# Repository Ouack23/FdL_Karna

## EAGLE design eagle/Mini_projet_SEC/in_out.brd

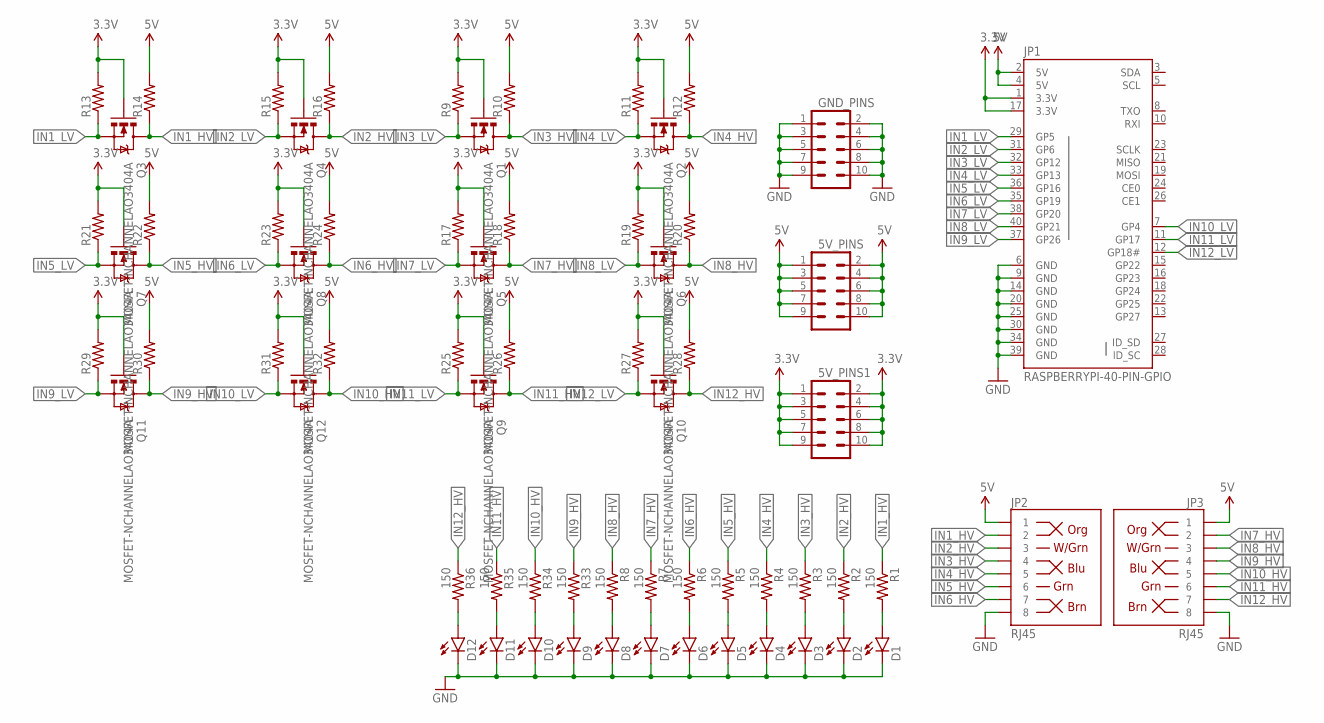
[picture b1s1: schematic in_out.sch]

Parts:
5V_PINS, 5V_PINS1: M05X2PTH; AVR_ICSP
D1, D2, D3, D4, D5, D6, D7, D8, D9, D10, D11, D12: LED5MM
GND_PINS: M05X2PTH; AVR_ICSP
JP1: RASPBERRYPI-40-PIN-GPIO; 2X20-SHROUDED
JP2, JP3: RJ45; RJ45-8
Q1, Q2, Q3, Q4, Q5, Q6, Q7, Q8, Q9, Q10, Q11, Q12: MOSFET-NCHANNELAO3404A; SOT23-3
R1, R2, R3, R4, R5, R6, R7, R8, R33, R34, R35, R36: 150; AXIAL-0.3EZ
R9, R10, R11, R12, R13, R14, R15, R16, R17, R18, R19, R20, R21, R22, R23, R24, R25, R26, R27, R28, R29, R30, R31, R32: RESISTORPTH-1/4W; AXIAL-0.4

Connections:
3.3V: 5V_PINS1.1, 5V_PINS1.2, 5V_PINS1.3, 5V_PINS1.4, 5V_PINS1.5, 5V_PINS1.6, 5V_PINS1.7, 5V_PINS1.8, 5V_PINS1.9, 5V_PINS1.10, JP1.1 (3.3V), JP1.17 (3.3V), Q1.1 (G), Q2.1 (G), Q3.1 (G), Q4.1 (G), Q5.1 (G), Q6.1 (G), Q7.1 (G), Q8.1 (G), Q9.1 (G), Q10.1 (G), Q11.1 (G), Q12.1 (G), R9.P$2 (2), R11.P$2 (2), R13.P$2 (2), R15.P$2 (2), R17.P$2 (2), R19.P$2 (2), R21.P$2 (2), R23.P$2 (2), R25.P$2 (2), R27.P$2 (2), R29.P$2 (2), R31.P$2 (2)
5V: 5V_PINS.1, 5V_PINS.2, 5V_PINS.3, 5V_PINS.4, 5V_PINS.5, 5V_PINS.6, 5V_PINS.7, 5V_PINS.8, 5V_PINS.9, 5V_PINS.10, JP1.2 (5V), JP1.4 (5V), JP2.1, JP3.1, R10.P$2 (2), R12.P$2 (2), R14.P$2 (2), R16.P$2 (2), R18.P$2 (2), R20.P$2 (2), R22.P$2 (2), R24.P$2 (2), R26.P$2 (2), R28.P$2 (2), R30.P$2 (2), R32.P$2 (2)
GND: D1.K (C), D2.K (C), D3.K (C), D4.K (C), D5.K (C), D6.K (C), D7.K (C), D8.K (C), D9.K (C), D10.K (C), D11.K (C), D12.K (C), GND_PINS.1, GND_PINS.2, GND_PINS.3, GND_PINS.4, GND_PINS.5, GND_PINS.6, GND_PINS.7, GND_PINS.8, GND_PINS.9, GND_PINS.10, JP1.6 (GND), JP1.9 (GND), JP1.14 (GND), JP1.20 (GND), JP1.25 (GND), JP1.30 (GND), JP1.34 (GND), JP1.39 (GND), JP2.8, JP3.8
IN1_HV: JP2.2, Q3.3 (D), R1.P$1 (1), R14.P$1 (1)
IN1_LV: JP1.29 (GP5), Q3.2 (S), R13.P$1 (1)
IN2_HV: JP2.3, Q4.3 (D), R2.P$1 (1), R16.P$1 (1)
IN2_LV: JP1.31 (GP6), Q4.2 (S), R15.P$1 (1)
IN3_HV: JP2.4, Q1.3 (D), R3.P$1 (1), R10.P$1 (1)
IN3_LV: JP1.32 (GP12), Q1.2 (S), R9.P$1 (1)
IN4_HV: JP2.5, Q2.3 (D), R4.P$1 (1), R12.P$1 (1)
IN4_LV: JP1.33 (GP13), Q2.2 (S), R11.P$1 (1)
IN5_HV: JP2.6, Q7.3 (D), R5.P$1 (1), R22.P$1 (1)
IN5_LV: JP1.36 (GP16), Q7.2 (S), R21.P$1 (1)
IN6_HV: JP2.7, Q8.3 (D), R6.P$1 (1), R24.P$1 (1)
IN6_LV: JP1.35 (GP19), Q8.2 (S), R23.P$1 (1)
IN7_HV: JP3.2, Q5.3 (D), R7.P$1 (1), R18.P$1 (1)
IN7_LV: JP1.38 (GP20), Q5.2 (S), R17.P$1 (1)
IN8_HV: JP3.3, Q6.3 (D), R8.P$1 (1), R20.P$1 (1)
IN8_LV: JP1.40 (GP21), Q6.2 (S), R19.P$1 (1)
IN9_HV: JP3.4, Q11.3 (D), R30.P$1 (1), R33.P$1 (1)
IN9_LV: JP1.37 (GP26), Q11.2 (S), R29.P$1 (1)
IN10_HV: JP3.5, Q12.3 (D), R32.P$1 (1), R34.P$1 (1)
IN10_LV: JP1.7 (GP4), Q12.2 (S), R31.P$1 (1)
IN11_HV: JP3.6, Q9.3 (D), R26.P$1 (1), R35.P$1 (1)
IN11_LV: JP1.11 (GP17), Q9.2 (S), R25.P$1 (1)
IN12_HV: JP3.7, Q10.3 (D), R28.P$1 (1), R36.P$1 (1)
IN12_LV: JP1.12 (GP18#), Q10.2 (S), R27.P$1 (1)
unnamed: D9.A, R33.P$2 (2)
unnamed: D10.A, R34.P$2 (2)
unnamed: D1.A, R1.P$2 (2)
unnamed: D2.A, R2.P$2 (2)
unnamed: D3.A, R3.P$2 (2)
unnamed: D4.A, R4.P$2 (2)
unnamed: D5.A, R5.P$2 (2)
unnamed: D6.A, R6.P$2 (2)
unnamed: D7.A, R7.P$2 (2)
unnamed: D8.A, R8.P$2 (2)
unnamed: D11.A, R35.P$2 (2)
unnamed: D12.A, R36.P$2 (2)

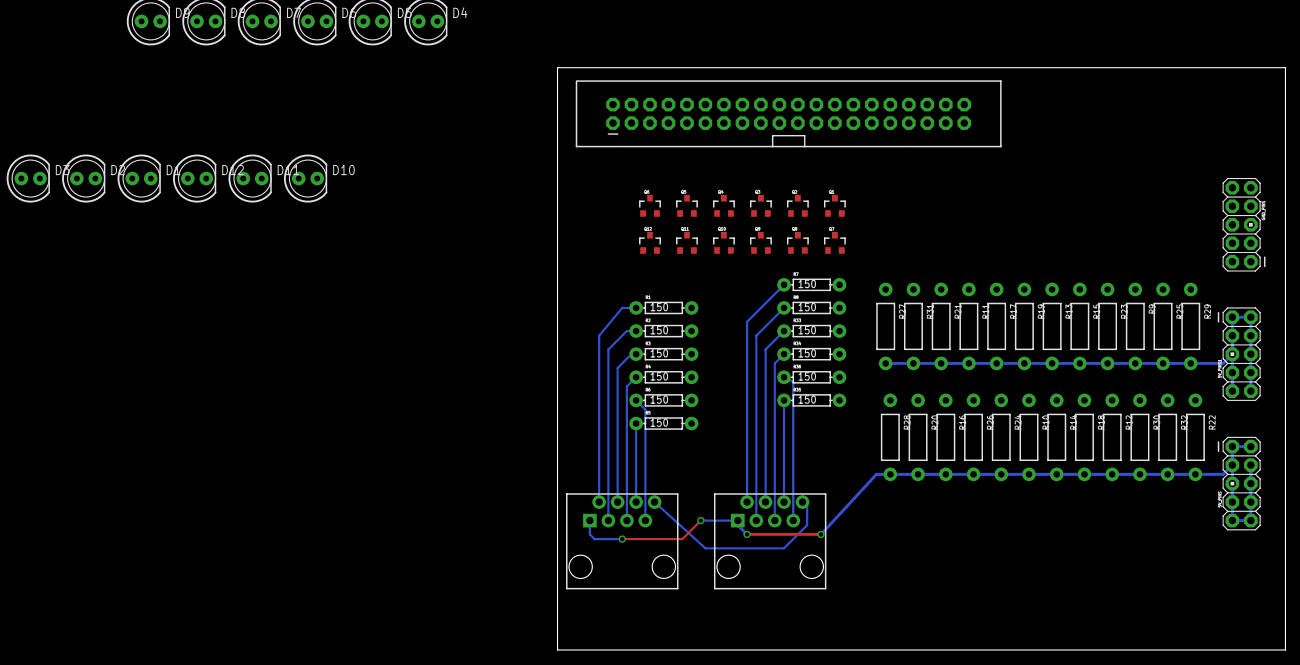
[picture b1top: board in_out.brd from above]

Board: 2 copper layers, 100.0 x 80.0 mm, 66 parts (0 on the bottom side), 39 nets.

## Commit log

2016-11-03 Add eagle library (PCB software)
2016-11-03 Add Viking project to repo
2016-11-07 First main.py
2016-11-10 Setting proper acces rights for all files on RPi
2016-11-17 Update Eagle files. First usable PCB card base
2016-12-02 First DMX test Creation of develop branch for testing purpose
2016-12-02 First working DMX Scenario Implementation of changing colors, abrupt and fades Add log classes for convenience and lisibility Removal of all GPIO code for me to be able to test on PC and not on RPi
2017-01-05 Change gitignore to ignore pyc files
2017-01-07 Refactor project Starting OSC integration DMX fade doesn't work
2017-01-08 Working parallel OSC / DMX
2017-01-11 Auto start ola if not the case
2017-01-11 Creation of games directory, which will contain all games python files Auto-kill already started python2 instances when OSC cannot run Creation of game_manager, which will be called by main. Can chan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
2017-01-13 Adding pins.py file to declare RPi.GPIO setup functions
2017-01-13 Edit Main
2017-01-13 Creation of shell file to launch program
2017-01-13 Change pins.py
2017-01-13 First try with RPi.GPIO as light output
2017-01-13 Various optimizations for pins.py, continuing dev
2017-01-13 First instanciation of GPIO event detecions
2017-01-14 Minor fixes (pycharm warnings)
2017-01-15 First implementation of Simon game with DMX + keyboard.
2017-01-15 First implementation of RPI Simon game
2017-01-15 Debug of simon gpio implementation, but SEGFAULT sometimes ...
2017-01-15 Minor changes
2017-01-20 Adding pins.py file to declare RPi.GPIO setup functions
    Edit Main
    Creation of shell file to launch program
    Change pins.py
    First try with RPi.GPIO as light output
    Various optimizations for pins.py, continuing dev
    First instanciation of GPIO event detecions
2017-01-20 Fully functional Simon
2017-01-27 Final Simon commit. Fail info during game before restart.

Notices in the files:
parts and their libraries:
SparkFun-Connectors: Licensing: Creative Commons ShareAlike 4.0 International - https://creativecommons.org/licenses/by-sa/4.0
